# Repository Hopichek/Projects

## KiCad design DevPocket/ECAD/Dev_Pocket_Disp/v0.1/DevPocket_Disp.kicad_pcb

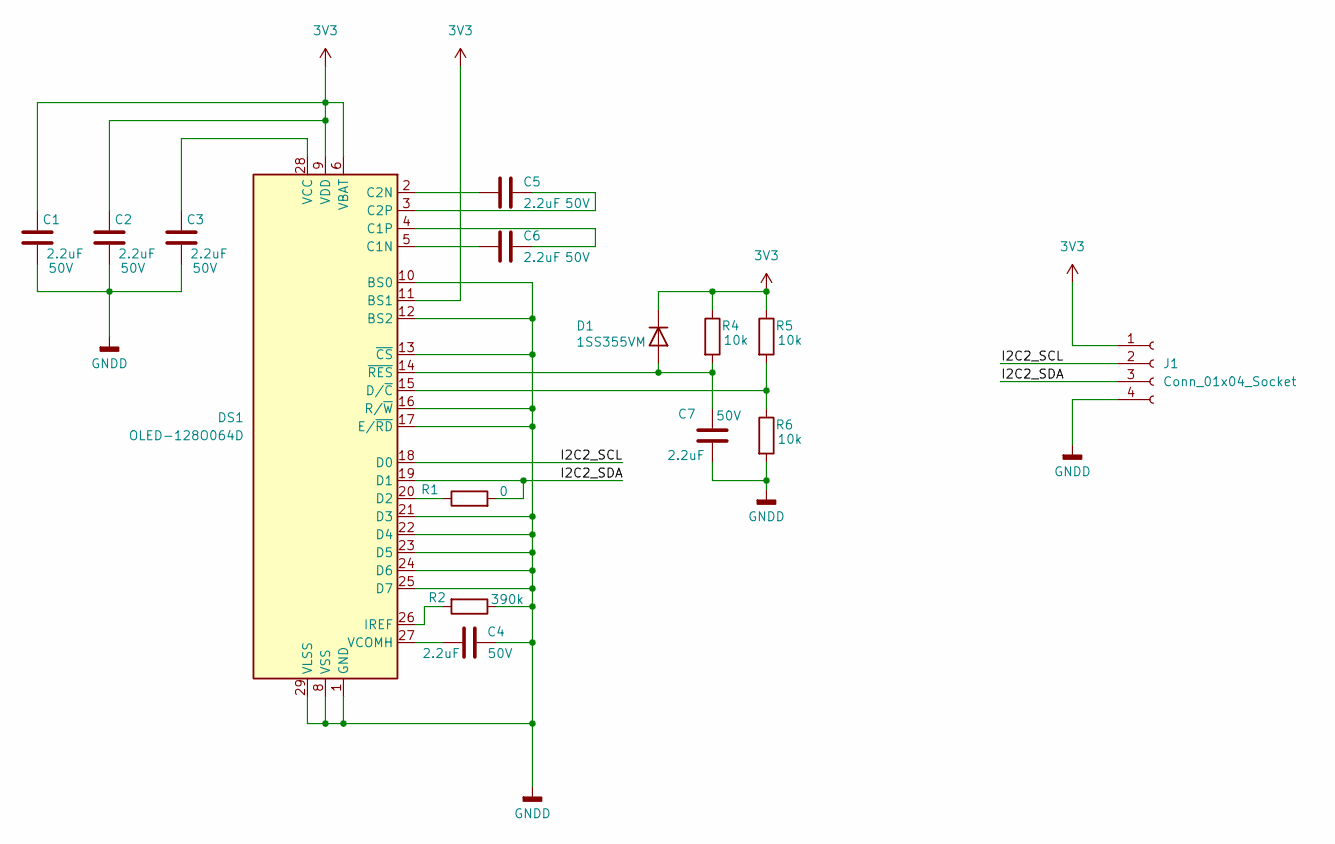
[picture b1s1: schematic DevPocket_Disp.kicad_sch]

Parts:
C1, C2, C3, C4, C5, C6, C7: 2.2uF; C_0603_1608Metric; Voltage 50V
D1: 1SS355VM; D_SOD-323F
DS1: OLED-128O064D
J1: Conn_01x04_Socket; PinHeader_1x04_P2.54mm_Vertical
R1: 0; R_0603_1608Metric
R2: 390k; R_0603_1608Metric
R4, R5, R6: 10k; R_0603_1608Metric

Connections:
3V3: C1.2, C2.2, D1.1 (K), DS1.6 (VBAT), DS1.9 (VDD), DS1.11 (BS1), J1.1, R4.1, R5.1
/I2C2_SCL: DS1.18 (D0), J1.2
/I2C2_SDA: DS1.19 (D1), J1.3, R1.2
GNDD: C1.1, C2.1, C3.1, C4.2, C7.1, DS1.1 (GND), DS1.8 (VSS), DS1.10 (BS0), DS1.12 (BS2), DS1.13 (~CS), DS1.16 (R/~W), DS1.17 (E/~RD), DS1.21 (D3), DS1.22 (D4), DS1.23 (D5), DS1.24 (D6), DS1.25 (D7), DS1.29 (VLSS), DS1.30 (GND), J1.4, R2.1, R6.2
unnamed: C7.2, D1.2 (A), DS1.14 (~RES), R4.2
unnamed: C6.1, DS1.5 (C1N)
unnamed: C6.2, DS1.4 (C1P)
unnamed: C5.1, DS1.2 (C2N)
unnamed: C5.2, DS1.3 (C2P)
unnamed: DS1.20 (D2), R1.1
unnamed: DS1.15 (D/~C), R5.2, R6.1
unnamed: DS1.26 (IREF), R2.2
unnamed: C3.2, DS1.28 (VCC)
unnamed: C4.1, DS1.27 (VCOMH)

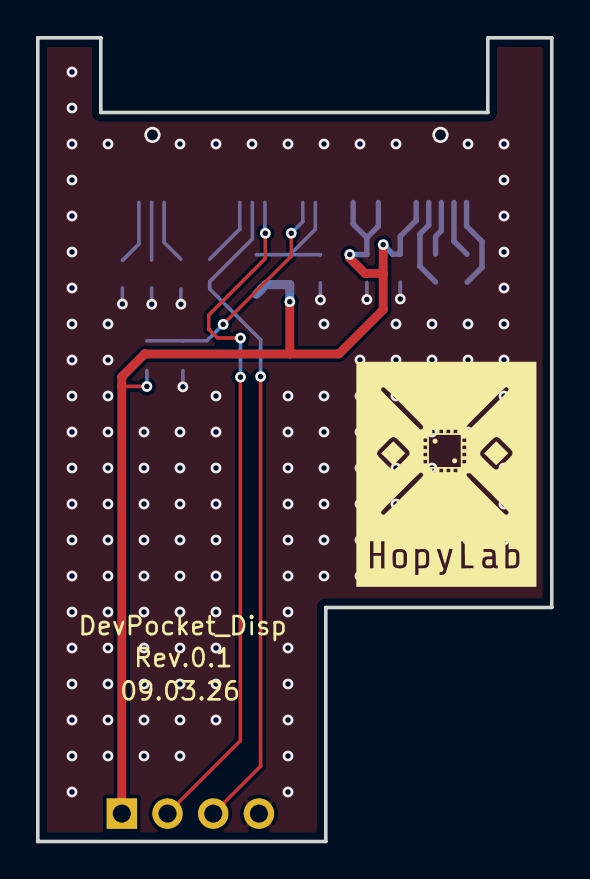
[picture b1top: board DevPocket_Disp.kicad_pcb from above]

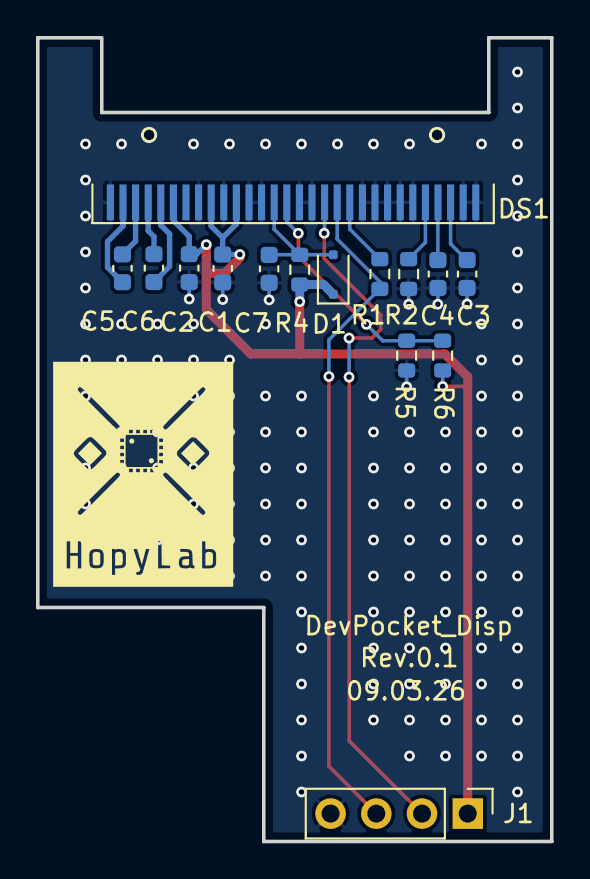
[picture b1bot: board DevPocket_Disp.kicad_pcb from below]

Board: 2 copper layers, 28.6 x 44.7 mm, 15 parts (15 on the bottom side), 14 nets.

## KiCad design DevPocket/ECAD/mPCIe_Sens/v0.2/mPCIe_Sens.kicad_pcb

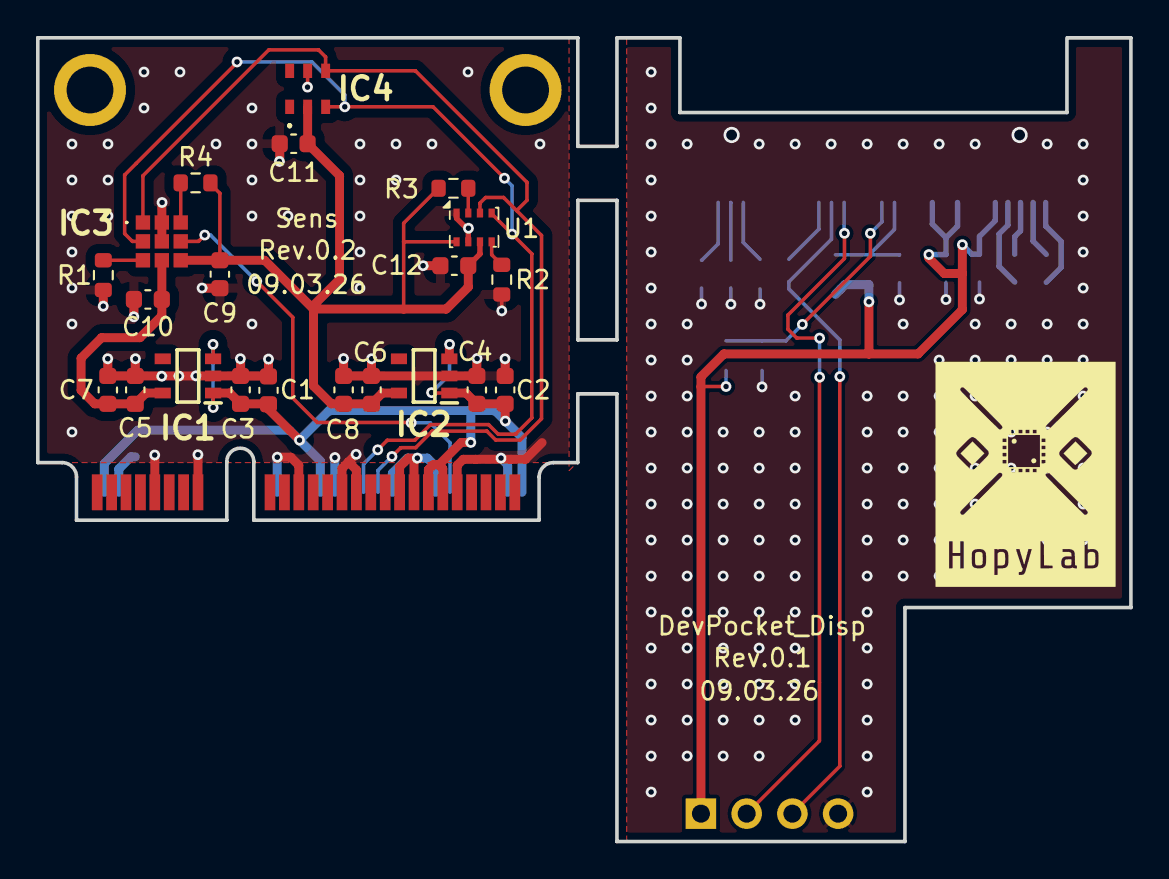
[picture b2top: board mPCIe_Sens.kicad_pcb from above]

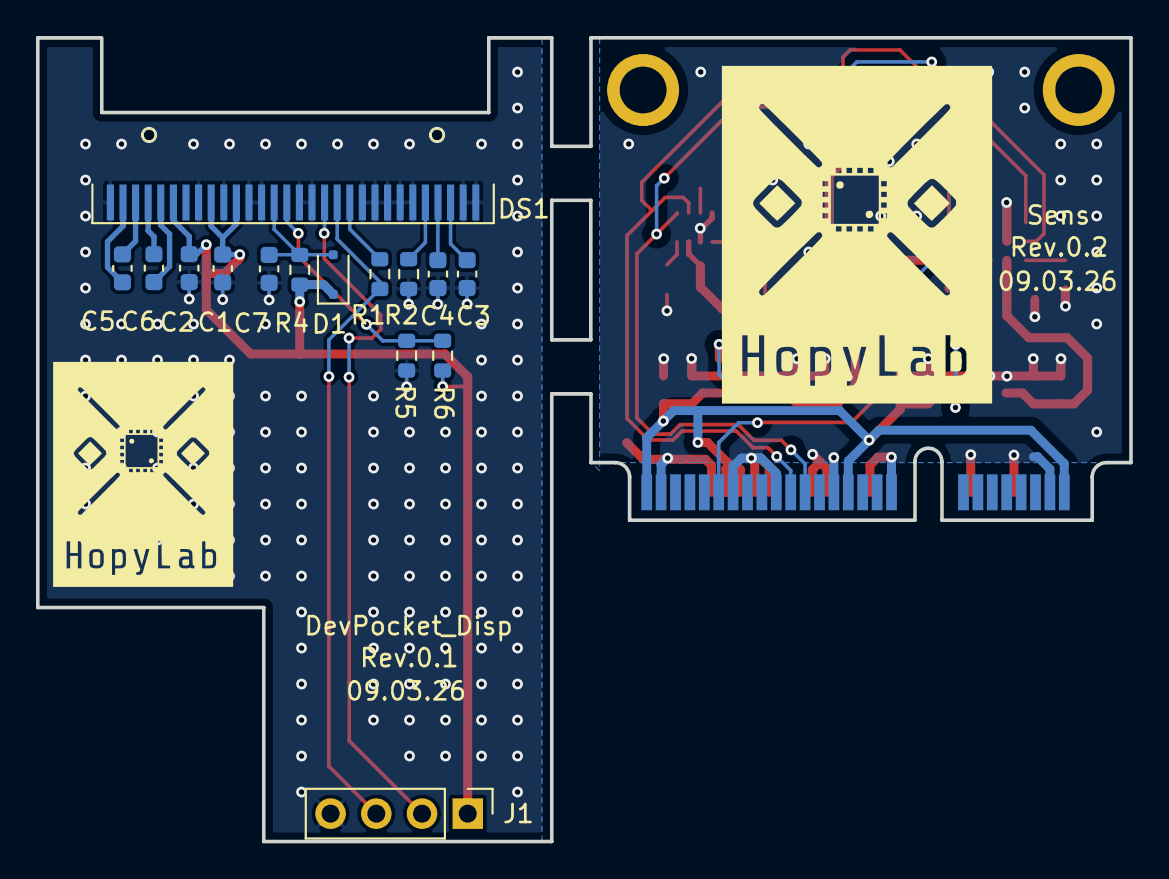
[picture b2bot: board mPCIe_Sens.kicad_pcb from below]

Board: 2 copper layers, 60.7 x 44.7 mm, 37 parts (15 on the bottom side), 24 nets.

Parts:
C1, C2, C5, C6, C10: 10uF; C_0603_1608Metric
C1#2, C2#2, C3#2, C4#2, C5#2, C6#2, C7#2: 2.2uF; C_0603_1608Metric
C3, C4, C7, C8, C9, C11, C12: 100nF; C_0603_1608Metric
D1: mPCIe_Card_Half; mpcie-half-card
D1#2: 1SS355VM; D_SOD-323F
DS1: OLED-128O064D
IC1: XC6219B182MR-G; SOT95P280X130-5N
IC2: XC6219B332MR-G; SOT95P280X130-5N
IC3: ENS160-BGLM; ENS160BGLM
IC4: AHT20
J1: Conn_01x04_Socket; PinHeader_1x04_P2.54mm_Vertical
R1, R2, R3, R4, R4#2, R5, R6: 10k; R_0603_1608Metric
R1#2: 0; R_0603_1608Metric
R2#2: 390k; R_0603_1608Metric
U1: BMP280; Bosch_LGA-8_2x2.5mm_P0.65mm_ClockwisePinNumbering

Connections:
1V8: C5.2, C7.2, C10.2, IC1.5 (VOUT), IC3.4 (VDD)
3V3: C1#2.2, C2#2.2, C6.2, C8.2, C9.2, C11.2, C12.2, D1#2.1 (K), DS1.6 (VBAT), DS1.9 (VDD), DS1.11 (BS1), IC2.5 (VOUT), IC3.5 (VDDIO_), IC4.2 (VDD), J1.1, R3.2, R4.2, R4#2.1, R5.1, U1.6 (VDDIO), U1.8 (VDD)
5V: C1.2, C2.2, C3.2, C4.2, D1.2, D1.24, D1.39, D1.41, D1.52, IC1.1 (VIN), IC1.3 (CE), IC2.1 (VIN), IC2.3 (CE)
/I2C2_SCL: DS1.18 (D0), J1.2
/I2C2_SDA: DS1.19 (D1), J1.3, R1#2.2
/I2C_SCL: D1.30, IC3.2 (SCLK_/_SCL_), IC4.3 (SCL), U1.4 (SCK)
/I2C_SDA: D1.32, IC3.1 (MOSI_/_SDA), IC4.4 (SDA), U1.3 (SDI)
/INT_ENS: D1.42, IC3.6 (INTN_)
GND: C1.1, C2.1, C3.1, C4.1, C5.1, C6.1, C7.1, C8.1, C9.1, C10.1, C11.1, C12.1, D1.4, D1.9, D1.15, D1.18, D1.21, D1.26, D1.27, D1.29, D1.34, D1.35, D1.37, D1.40, D1.43, D1.50, IC1.2 (VSS), IC2.2 (VSS), IC3.8 (VSS__1), IC3.9 (VSS__2), IC4.5 (GND), R1.1, R2.1, U1.1 (GND), U1.7 (GND)
GNDD: C1#2.1, C2#2.1, C3#2.1, C4#2.2, C7#2.1, DS1.1 (GND), DS1.8 (VSS), DS1.10 (BS0), DS1.12 (BS2), DS1.13 (~CS), DS1.16 (R/~W), DS1.17 (E/~RD), DS1.21 (D3), DS1.22 (D4), DS1.23 (D5), DS1.24 (D6), DS1.25 (D7), DS1.29 (VLSS), DS1.30 (GND), J1.4, R2#2.1, R6.2
unnamed: C7#2.2, D1#2.2 (A), DS1.14 (~RES), R4#2.2
unnamed: C6#2.1, DS1.5 (C1N)
unnamed: C6#2.2, DS1.4 (C1P)
unnamed: C5#2.1, DS1.2 (C2N)
unnamed: C5#2.2, DS1.3 (C2P)
unnamed: DS1.20 (D2), R1#2.1
unnamed: DS1.15 (D/~C), R5.2, R6.1
unnamed: DS1.26 (IREF), R2#2.2
unnamed: C3#2.2, DS1.28 (VCC)
unnamed: C4#2.1, DS1.27 (VCOMH)
unnamed: IC3.7 (CSN), R4.1
unnamed: IC3.3 (MISO_/_ADDR), R1.2
unnamed: R3.1, U1.2 (CSB)
unnamed: R2.2, U1.5 (SDO)

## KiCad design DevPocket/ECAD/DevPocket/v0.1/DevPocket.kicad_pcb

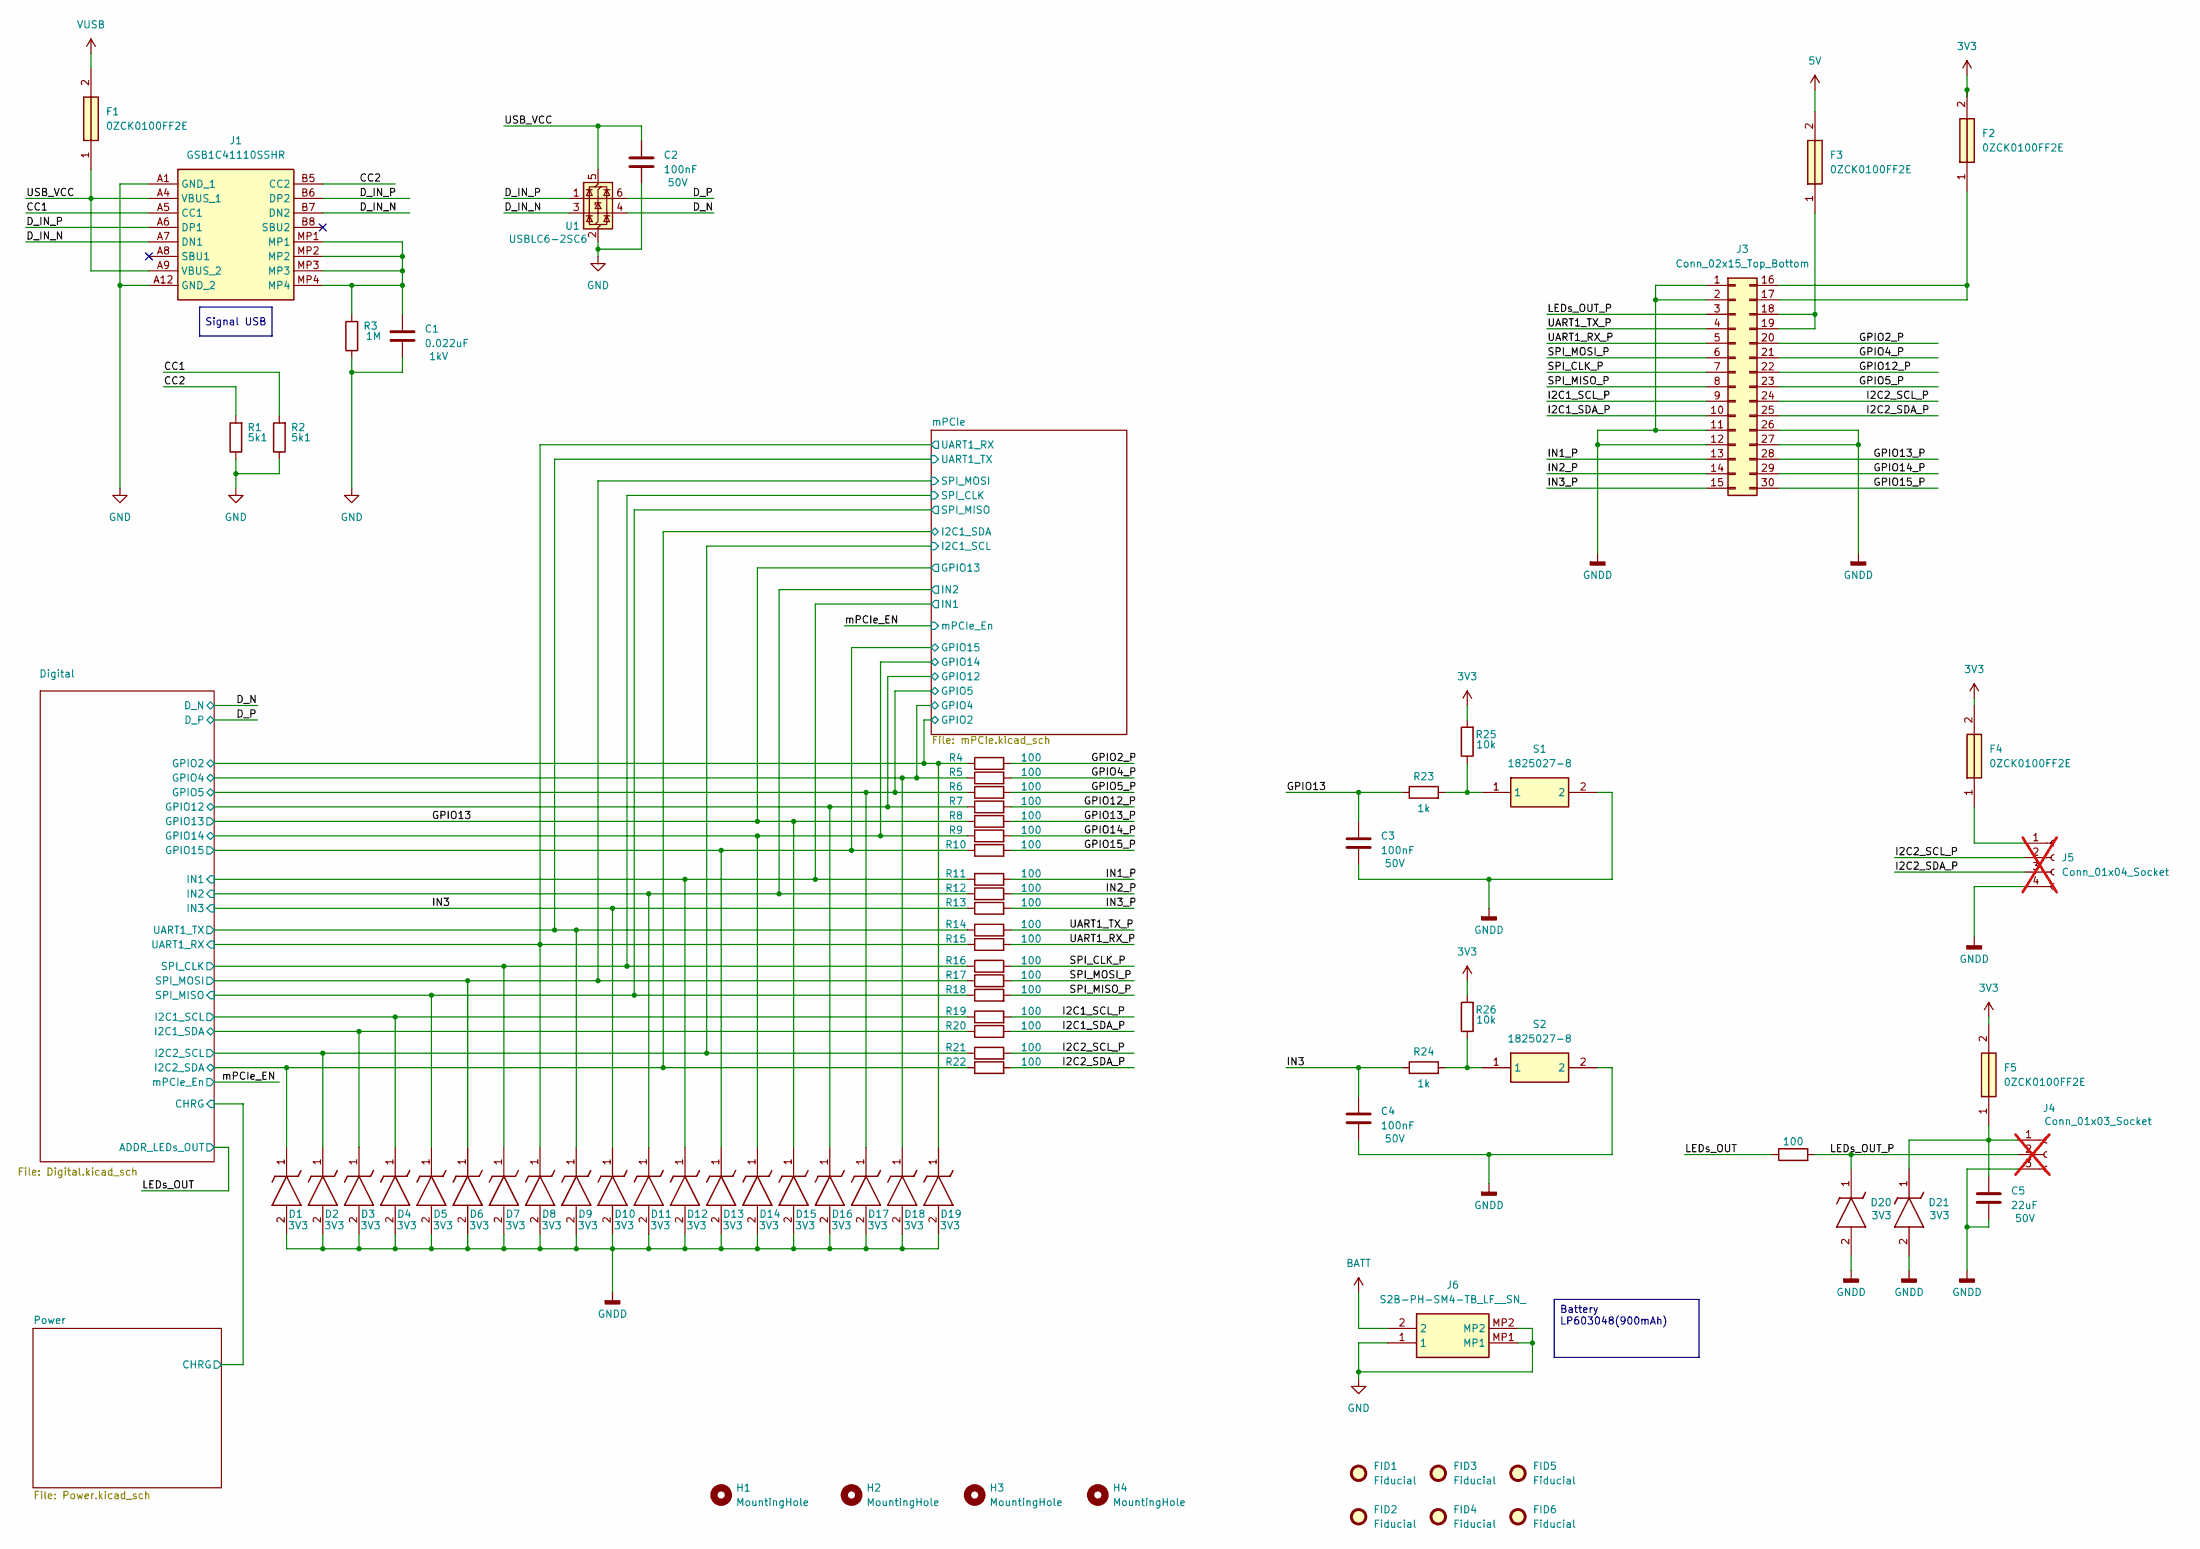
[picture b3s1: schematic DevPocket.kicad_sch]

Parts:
C1: 0.022uF; C_1210_3225Metric; Voltage 1kV
C2, C3, C4: 100nF; C_0603_1608Metric; Voltage 50V
C5: 22uF; C_0805_2012Metric; Voltage 50V
D1, D2, D3, D4, D5, D6, D7, D8, D9, D10, D11, D12, D13, D14, D15, D16, D17, D18, D19, D20, D21: UCLAMP3301D.TCT; SOD2613X117N; Voltage 3V3; Manufacturer_Part_Number UCLAMP3301D.TCT; Mouser Part Number 947-UCLAMP3301D.TCT
F1, F2, F3, F4, F5: 0ZCK0100FF2E; FUSC2214X180N; Manufacturer_Part_Number 0ZCK0100FF2E; Mouser Part Number 530-0ZCK0100FF2E
FID1, FID2, FID3, FID4, FID5, FID6: Fiducial; Fiducial_0.5mm_Mask1mm
H1, H2, H3, H4: MountingHole; MountingHole_2.2mm_M2_ISO14580
J1: GSB1C41110SSHR; Manufacturer_Part_Number GSB1C41110SSHR
J3: Conn_02x15_Top_Bottom; PinSocket_2x15_P2.54mm_Horizontal
J4: Conn_01x03_Socket; PinSocket_1x03_P2.54mm_Vertical; not fitted
J5: Conn_01x04_Socket; PinSocket_1x04_P2.54mm_Vertical; not fitted
J6: S2B-PH-SM4-TB_LF__SN_; S2BPHSM4TBLFSN; Manufacturer_Part_Number S2B-PH-SM4-TB(LF)(SN); Mouser Part Number N/A
R1, R2: 5k1; R_0603_1608Metric
R3: 1M; R_0805_2012Metric
R4, R5, R6, R7, R8, R9, R10, R11, R12, R13, R14, R15, R16, R17, R18, R19, R20, R21, R22, R27: 100; R_0603_1608Metric
R23, R24: 1k; R_0603_1608Metric
R25, R26: 10k; R_0603_1608Metric
S1, S2: 1825027-8; Manufacturer_Part_Number 1825027-8; Mouser Part Number 506-1825027-8
U1: USBLC6-2SC6; SOT-23-6

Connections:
3V3: F2.2, F4.2, F5.2, R25.2, R26.2; also elsewhere on the board
5V: F3.2; also elsewhere on the board
/CC1: J1.A5 (CC1), R2.2
/CC2: J1.B5 (CC2), R1.2
/D_IN_N: J1.A7 (DN1), J1.B7 (DN2), U1.3 (I/O2)
/D_IN_P: J1.A6 (DP1), J1.B6 (DP2), U1.1 (I/O1)
/D_N: U1.4 (I/O2); also elsewhere on the board
/D_P: U1.6 (I/O1); also elsewhere on the board
/Digital/GPIO2: D19.1 (K), R4.1; also elsewhere on the board
/Digital/GPIO4: D18.1 (K), R5.1; also elsewhere on the board
/Digital/GPIO5: D17.1 (K), R6.1; also elsewhere on the board
/Digital/GPIO14: D14.1 (K), R9.1; also elsewhere on the board
/Digital/GPIO15: D13.1 (K), R10.1; also elsewhere on the board
/Digital/I2C1_SCL: D4.1 (K), R19.1; also elsewhere on the board
/Digital/I2C1_SDA: D3.1 (K), R20.1; also elsewhere on the board
/Digital/I2C2_SCL: D2.1 (K), R21.1; also elsewhere on the board
/Digital/I2C2_SDA: D1.1 (K), R22.1; also elsewhere on the board
/Digital/IN1: D12.1 (K), R11.1; also elsewhere on the board
/Digital/IN2: D11.1 (K), R12.1; also elsewhere on the board
/Digital/SPI_CLK: D7.1 (K), R16.1; also elsewhere on the board
/Digital/SPI_MISO: D5.1 (K), R18.1; also elsewhere on the board
/Digital/SPI_MOSI: D6.1 (K), R17.1; also elsewhere on the board
/Digital/UART1_RX: D8.1 (K), R15.1; also elsewhere on the board
/Digital/UART1_TX: D9.1 (K), R14.1; also elsewhere on the board
/GPIO2_P: J3.20, R4.2
/GPIO4_P: J3.21, R5.2
/GPIO5_P: J3.23, R6.2
/GPIO12_P: J3.22, R7.2
/GPIO13: C3.1, D15.1 (K), R8.1, R23.1; also elsewhere on the board
/GPIO13_P: J3.28, R8.2
/GPIO14_P: J3.29, R9.2
/GPIO15_P: J3.30, R10.2
/I2C1_SCL_P: J3.9, R19.2
/I2C1_SDA_P: J3.10, R20.2
/I2C2_SCL_P: J3.24, J5.2, R21.2
/I2C2_SDA_P: J3.25, J5.3, R22.2
/IN1_P: J3.13, R11.2
/IN2_P: J3.14, R12.2
/IN3: C4.1, D10.1 (K), R13.1, R24.1; also elsewhere on the board
/IN3_P: J3.15, R13.2
/LEDs_OUT: R27.1; also elsewhere on the board
/LEDs_OUT_P: D20.1 (K), J3.3, J4.2, R27.2
/SPI_CLK_P: J3.7, R16.2
/SPI_MISO_P: J3.8, R18.2
/SPI_MOSI_P: J3.6, R17.2
/UART1_RX_P: J3.5, R15.2
/UART1_TX_P: J3.4, R14.2
/USB_VCC: C2.1, F1.1, J1.A4 (VBUS_1), J1.A9 (VBUS_2), U1.5 (VBUS)
/mPCIe_EN: D16.1 (K), R7.1; also elsewhere on the board
BATT: J6.2; also elsewhere on the board
GND: C1.2, C2.2, C3.2, C4.2, C5.2, D1.2 (A), D2.2 (A), D3.2 (A), D4.2 (A), D5.2 (A), D6.2 (A), D7.2 (A), D8.2 (A), D9.2 (A), D10.2 (A), D11.2 (A), D12.2 (A), D13.2 (A), D14.2 (A), D15.2 (A), D16.2 (A), D17.2 (A), D18.2 (A), D19.2 (A), D20.2 (A), D21.2 (A), J1.A1 (GND_1), J1.A12 (GND_2), J3.1, J3.2, J3.11, J3.12, J3.26, J3.27, J4.3, J5.4, J6.1, J6.MP1, J6.MP2, R1.1, R2.1, R3.1, S1.2, S1.3, S1.4, S2.2, S2.3, S2.4, U1.2 (GND); also elsewhere on the board
unnamed: C1.1, J1.MP1, J1.MP2, J1.MP3, J1.MP4, R3.2
unnamed: C5.1, D21.1 (K), F5.1, J4.1
unnamed: F2.1, J3.16, J3.17
unnamed: F3.1, J3.18, J3.19
unnamed: F4.1, J5.1
unnamed: R23.2, R25.1, S1.1
unnamed: R24.2, R26.1, S2.1
VUSB: F1.2; also elsewhere on the board

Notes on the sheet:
Battery LP603048(900mAh)
Signal USB

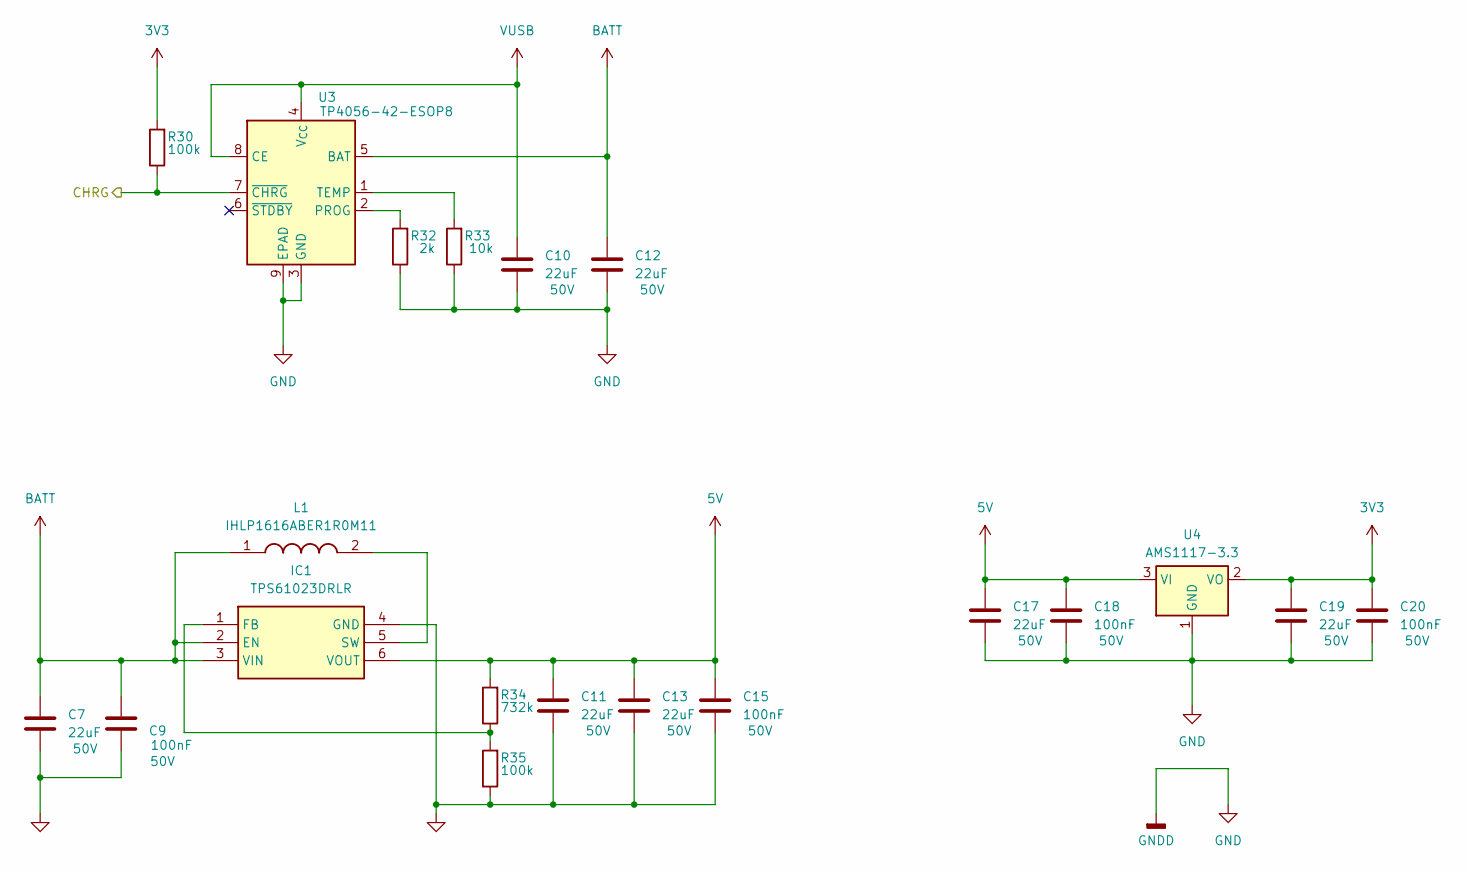
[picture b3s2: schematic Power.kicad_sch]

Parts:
C7, C10, C11, C12, C13, C17, C19: 22uF; C_0805_2012Metric; Voltage 50V
C9, C15, C18, C20: 100nF; C_0603_1608Metric; Voltage 50V
IC1: TPS61023DRLR; SOTFL50P160X60-6N; Manufacturer_Part_Number TPS61023DRLR; Mouser Part Number 595-TPS61023DRLR
L1: IHLP1616ABER1R0M11; INDPM4441X120N; Manufacturer_Part_Number IHLP1616ABER1R0M11; Mouser Part Number 70-IHLP1616ABER1R0M1
R30, R35: 100k; R_0603_1608Metric
R32: 2k; R_0603_1608Metric
R33: 10k; R_0603_1608Metric
R34: 732k; R_0603_1608Metric
U3: TP4056-42-ESOP8; SOIC-8-1EP_3.9x4.9mm_P1.27mm_EP2.29x3mm_ThermalVias
U4: AMS1117-3.3; SOT-223-3_TabPin2

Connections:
3V3: C19.1, C20.1, R30.2, U4.2 (VO); also elsewhere on the board
5V: C11.1, C13.1, C15.1, C17.1, C18.1, IC1.6 (VOUT), R34.2, U4.3 (VI); also elsewhere on the board
/Digital/CHRG: R30.1, U3.7 (~CHRG); also elsewhere on the board
BATT: C7.1, C9.1, C12.1, IC1.2 (EN), IC1.3 (VIN), L1.1, U3.5 (BAT); also elsewhere on the board
GND: C7.2, C9.2, C10.2, C11.2, C12.2, C13.2, C15.2, C17.2, C18.2, C19.2, C20.2, IC1.4 (GND), R32.1, R33.1, R35.1, U3.3 (GND), U3.9 (EPAD), U4.1 (GND); also elsewhere on the board
unnamed: IC1.1 (FB), R34.1, R35.2
unnamed: IC1.5 (SW), L1.2
unnamed: R32.2, U3.2 (PROG)
unnamed: R33.2, U3.1 (TEMP)
VUSB: C10.1, U3.4 (V_{CC}), U3.8 (CE); also elsewhere on the board

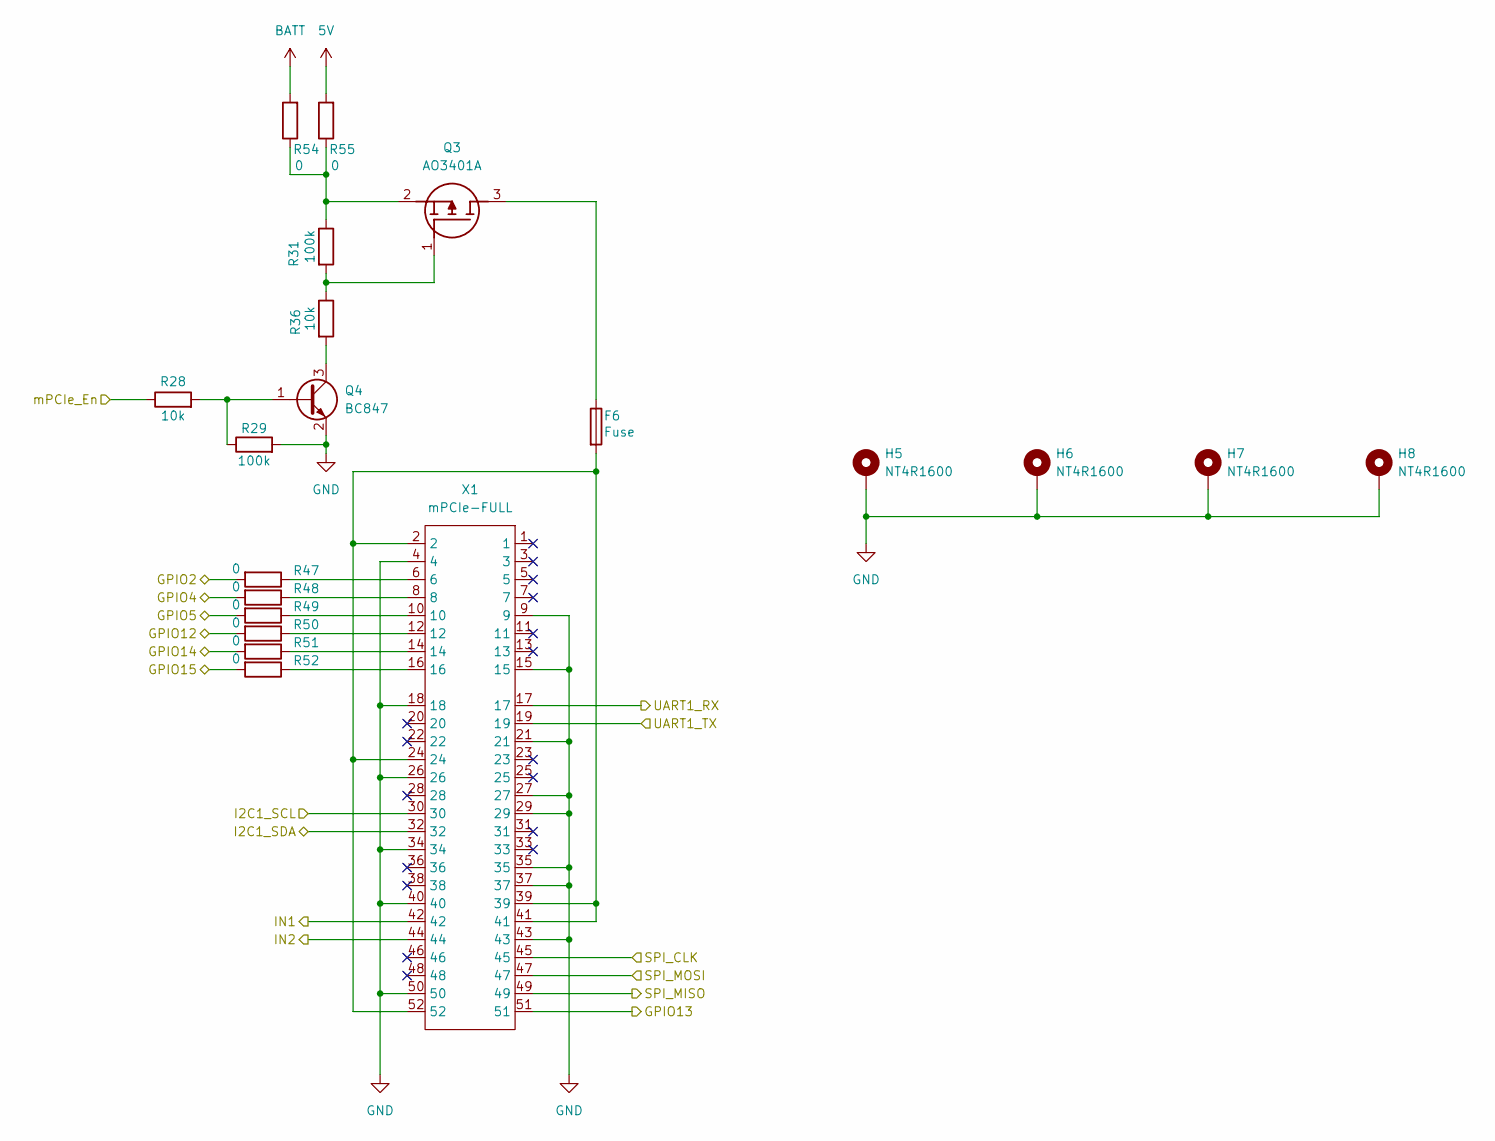
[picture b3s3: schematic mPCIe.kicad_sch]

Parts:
F6: Fuse; Fuse_0603_1608Metric
H5, H6, H7, H8: NT4R1600; MountingHole_2.5mm_Pad
Q3: AO3401A; SOT95P280X125-3N; Manufacturer_Part_Number AO3401A
Q4: BC847; SOT-23
R28, R36: 10k; R_0603_1608Metric
R29, R31: 100k; R_0603_1608Metric
R47, R48, R49, R50, R51, R52, R54, R55: 0; R_0603_1608Metric
X1: mPCIe-FULL; BUS_PCI_Express_Mini_Full

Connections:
5V: R55.2; also elsewhere on the board
/Digital/GPIO2: R47.2; also elsewhere on the board
/Digital/GPIO4: R48.2; also elsewhere on the board
/Digital/GPIO5: R49.2; also elsewhere on the board
/Digital/GPIO14: R51.2; also elsewhere on the board
/Digital/GPIO15: R52.2; also elsewhere on the board
/Digital/I2C2_SCL: X1.30; also elsewhere on the board
/Digital/I2C2_SDA: X1.32; also elsewhere on the board
/Digital/IN1: X1.42; also elsewhere on the board
/Digital/IN2: X1.44; also elsewhere on the board
/Digital/SPI_CLK: X1.45; also elsewhere on the board
/Digital/SPI_MISO: X1.49; also elsewhere on the board
/Digital/SPI_MOSI: X1.47; also elsewhere on the board
/Digital/UART1_RX: X1.17; also elsewhere on the board
/Digital/UART1_TX: X1.19; also elsewhere on the board
/GPIO13: X1.51; also elsewhere on the board
/mPCIe_EN: R28.1, R50.2; also elsewhere on the board
BATT: R54.2; also elsewhere on the board
GND: H5.1, H6.1, H7.1, H8.1, Q4.2 (E), R29.2, X1.4, X1.9, X1.15, X1.18, X1.21, X1.26, X1.27, X1.29, X1.34, X1.35, X1.37, X1.40, X1.43, X1.50, X1.MP; also elsewhere on the board
unnamed: F6.2, X1.2, X1.24, X1.39, X1.41, X1.52
unnamed: F6.1, Q3.3 (D)
unnamed: Q3.1 (G), R31.2, R36.1
unnamed: Q3.2 (S), R31.1, R54.1, R55.1
unnamed: Q4.1 (B), R28.2, R29.1
unnamed: Q4.3 (C), R36.2
unnamed: R47.1, X1.6
unnamed: R48.1, X1.8
unnamed: R49.1, X1.10
unnamed: R50.1, X1.12
unnamed: R51.1, X1.14
unnamed: R52.1, X1.16

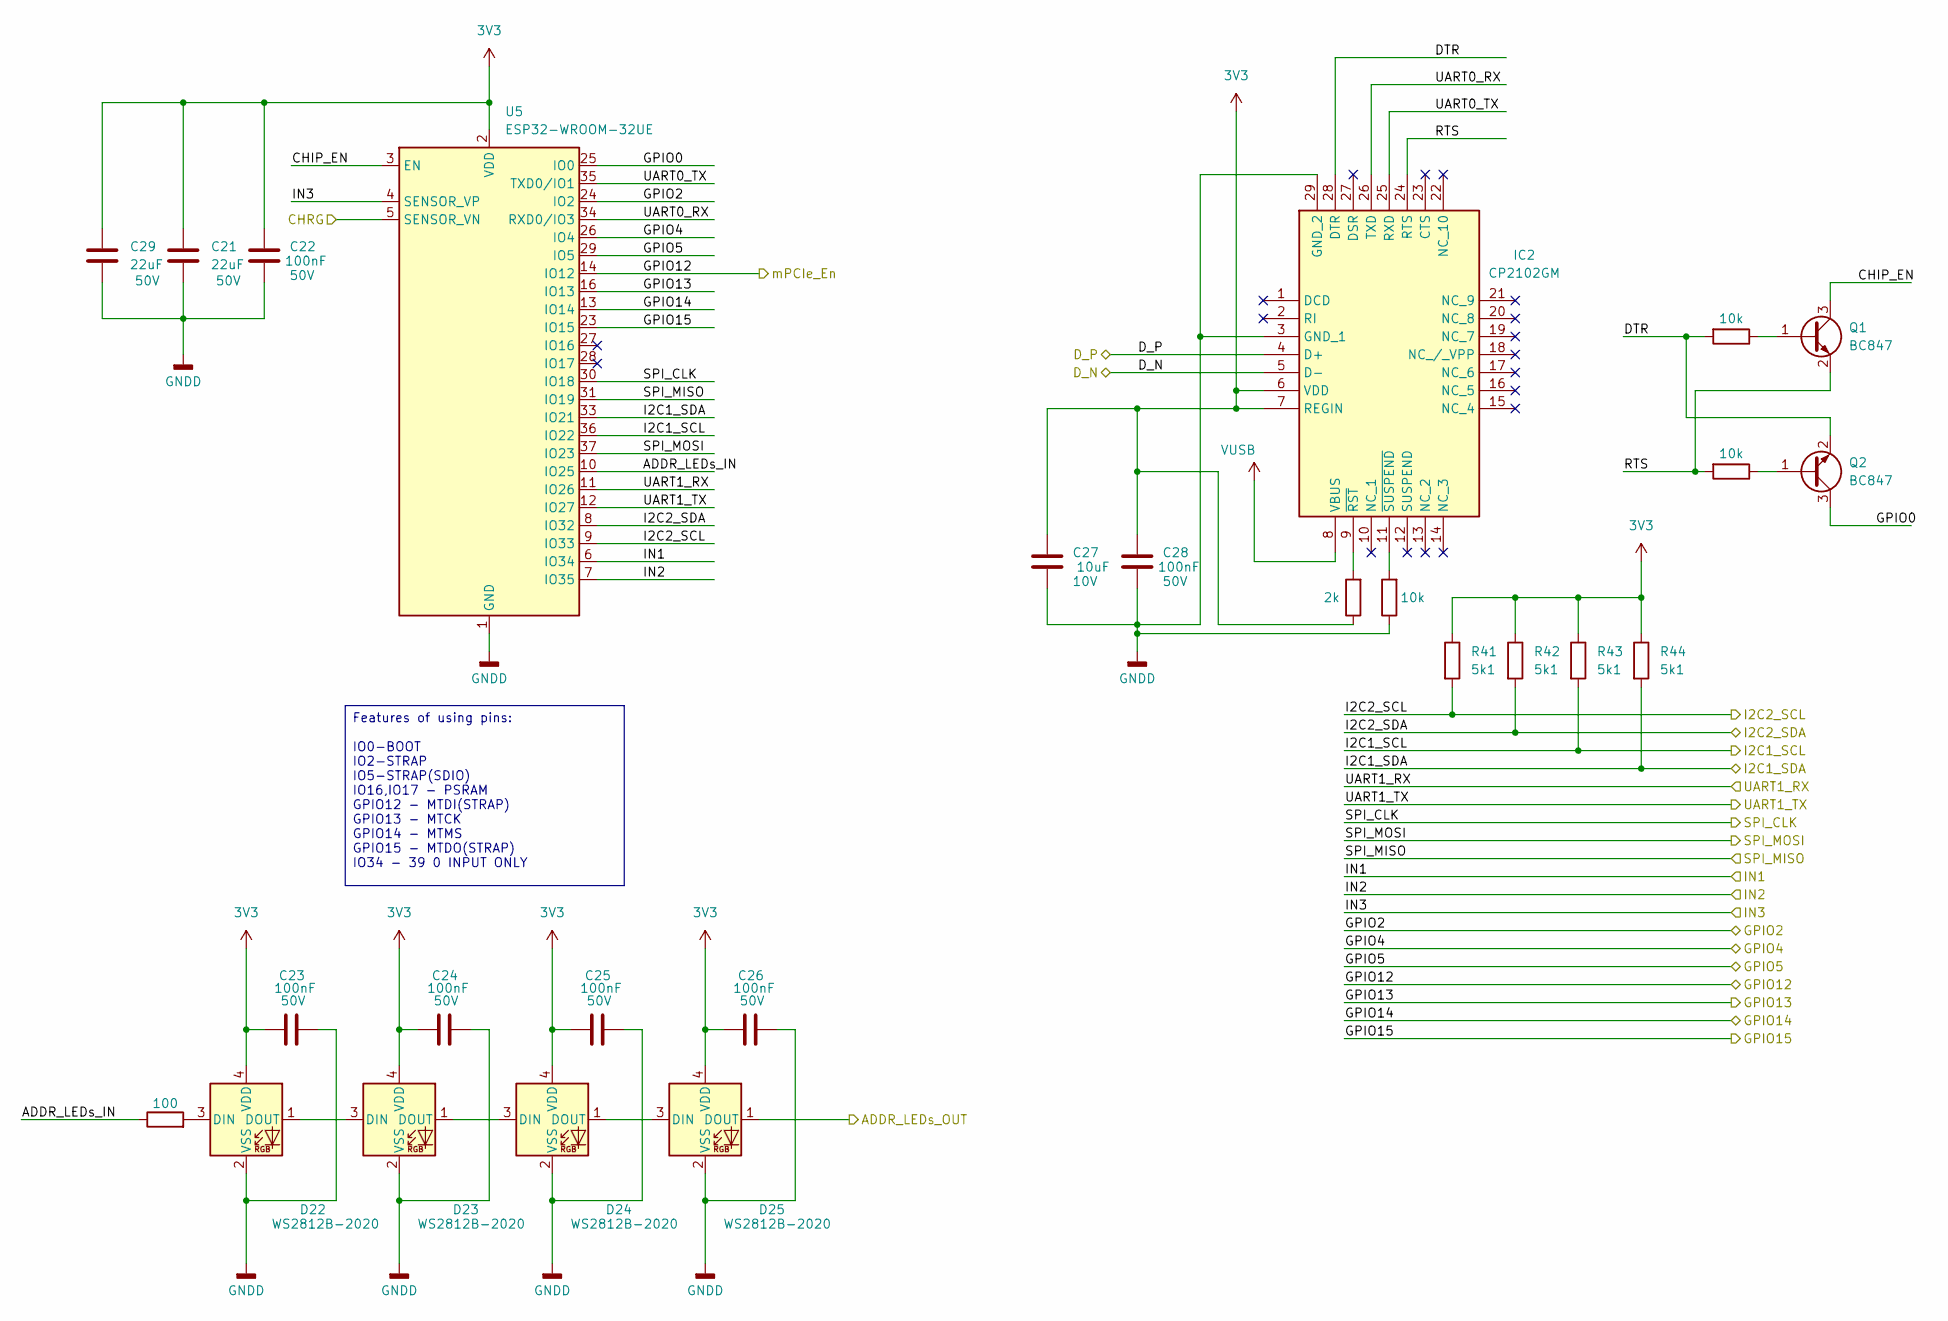
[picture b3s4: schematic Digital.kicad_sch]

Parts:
C21, C29: 22uF; C_0805_2012Metric; Voltage 50V
C22, C23, C24, C25, C26, C28: 100nF; C_0603_1608Metric; Voltage 50V
C27: 10uF; C_0603_1608Metric; Voltage 10V
D22, D23, D24, D25: WS2812B-2020; WS28122020
IC2: CP2102GM; QFN50P500X500X100-29N-D; Manufacturer_Part_Number CP2102GM
Q1, Q2: BC847; SOT-23
R38: 100; R_0603_1608Metric
R39: 2k; R_0603_1608Metric
R40, R45, R46: 10k; R_0603_1608Metric
R41, R42, R43, R44: 5k1; R_0603_1608Metric
U5: ESP32-WROOM-32UE; ESP32-WROOM-32U

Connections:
3V3: C21.1, C22.2, C23.1, C24.1, C25.1, C26.1, C27.2, C28.2, C29.1, D22.4 (VDD), D23.4 (VDD), D24.4 (VDD), D25.4 (VDD), IC2.6 (VDD), IC2.7 (REGIN), R39.1, R41.1, R42.1, R43.1, R44.1, U5.2 (VDD); also elsewhere on the board
/D_N: IC2.5 (D-); also elsewhere on the board
/D_P: IC2.4 (D+); also elsewhere on the board
/Digital/ADDR_LEDs_IN: R38.1, U5.10 (IO25)
/Digital/CHIP_EN: Q1.3 (C), U5.3 (EN)
/Digital/CHRG: U5.5 (SENSOR_VN); also elsewhere on the board
/Digital/DTR: IC2.28 (DTR), Q2.2 (E), R45.2
/Digital/GPIO0: Q2.3 (C), U5.25 (IO0)
/Digital/GPIO2: U5.24 (IO2); also elsewhere on the board
/Digital/GPIO4: U5.26 (IO4); also elsewhere on the board
/Digital/GPIO5: U5.29 (IO5); also elsewhere on the board
/Digital/GPIO14: U5.13 (IO14); also elsewhere on the board
/Digital/GPIO15: U5.23 (IO15); also elsewhere on the board
/Digital/I2C1_SCL: R43.2, U5.36 (IO22); also elsewhere on the board
/Digital/I2C1_SDA: R44.2, U5.33 (IO21); also elsewhere on the board
/Digital/I2C2_SCL: R41.2, U5.9 (IO33); also elsewhere on the board
/Digital/I2C2_SDA: R42.2, U5.8 (IO32); also elsewhere on the board
/Digital/IN1: U5.6 (IO34); also elsewhere on the board
/Digital/IN2: U5.7 (IO35); also elsewhere on the board
/Digital/RTS: IC2.24 (RTS), Q1.2 (E), R46.2
/Digital/SPI_CLK: U5.30 (IO18); also elsewhere on the board
/Digital/SPI_MISO: U5.31 (IO19); also elsewhere on the board
/Digital/SPI_MOSI: U5.37 (IO23); also elsewhere on the board
/Digital/UART0_RX: IC2.26 (TXD), U5.34 (RXD0/IO3)
/Digital/UART0_TX: IC2.25 (RXD), U5.35 (TXD0/IO1)
/Digital/UART1_RX: U5.11 (IO26); also elsewhere on the board
/Digital/UART1_TX: U5.12 (IO27); also elsewhere on the board
/GPIO13: U5.16 (IO13); also elsewhere on the board
/IN3: U5.4 (SENSOR_VP); also elsewhere on the board
/LEDs_OUT: D25.1 (DOUT); also elsewhere on the board
/mPCIe_EN: U5.14 (IO12); also elsewhere on the board
GND: C21.2, C22.1, C23.2, C24.2, C25.2, C26.2, C27.1, C28.1, C29.2, D22.2 (VSS), D23.2 (VSS), D24.2 (VSS), D25.2 (VSS), IC2.3 (GND_1), IC2.29 (GND_2), R40.1, U5.1 (GND), U5.15 (GND), U5.38 (GND), U5.39 (GND); also elsewhere on the board
unnamed: D22.3 (DIN), R38.2
unnamed: D22.1 (DOUT), D23.3 (DIN)
unnamed: D23.1 (DOUT), D24.3 (DIN)
unnamed: D24.1 (DOUT), D25.3 (DIN)
unnamed: IC2.9 (~RST), R39.2
unnamed: IC2.11 (~SUSPEND), R40.2
unnamed: Q1.1 (B), R45.1
unnamed: Q2.1 (B), R46.1
VUSB: IC2.8 (VBUS); also elsewhere on the board

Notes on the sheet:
Features of using pins: IO0-BOOT IO2-STRAP IO5-STRAP(SDIO) IO16,IO17 - PSRAM GPIO12 - MTDI(STRAP) GPIO13 - MTCK GPIO14 - MTMS GPIO15 - MTDO(STRAP) IO34 - 39 0 INPUT ONLY
